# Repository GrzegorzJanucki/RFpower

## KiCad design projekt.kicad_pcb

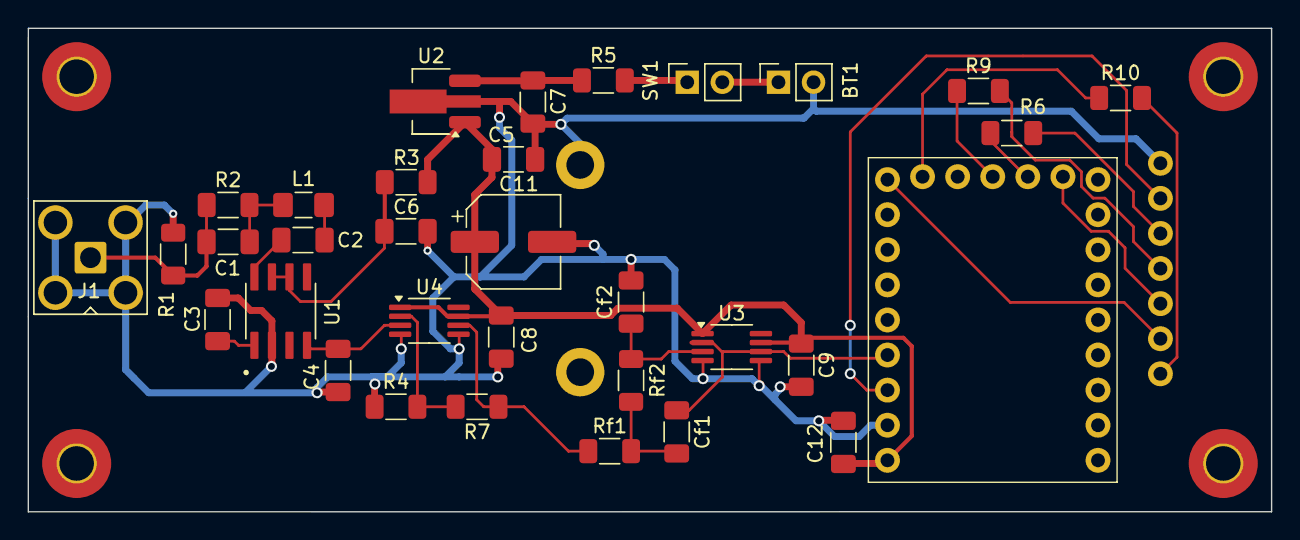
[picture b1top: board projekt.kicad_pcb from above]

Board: 2 copper layers, 90.0 x 35.0 mm, 34 parts (1 on the bottom side), 26 nets.

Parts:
BT1: 9V; PinSocket_1x02_P2.54mm_Vertical
C1: 15p; C_1206_3216Metric_Pad1.33x1.80mm_HandSolder
C2: 10n; C_1206_3216Metric_Pad1.33x1.80mm_HandSolder
C3, C4, C6, C8, C9, C12: 100n; C_1206_3216Metric_Pad1.33x1.80mm_HandSolder
C5, C7: 220n; C_1206_3216Metric_Pad1.33x1.80mm_HandSolder
C11: 10u; CP_Elec_6.3x5.3
Cf1, Cf2: 20n; C_1206_3216Metric_Pad1.33x1.80mm_HandSolder
J1: Conn_Coaxial; SMA_Amphenol_901-143_Horizontal
J2: OLED
L1: L; L_1206_3216Metric_Pad1.42x1.75mm_HandSolder
R1: 51; R_1206_3216Metric_Pad1.30x1.75mm_HandSolder
R2: 470; R_1206_3216Metric_Pad1.30x1.75mm_HandSolder
R3, R5: 6.8; R_1206_3216Metric_Pad1.30x1.75mm_HandSolder
R4: 3.3k; R_1206_3216Metric_Pad1.30x1.75mm_HandSolder
R6, R9, R10: 10; R_1206_3216Metric_Pad1.30x1.75mm_HandSolder
R7: 4.7k; R_1206_3216Metric_Pad1.30x1.75mm_HandSolder
RP2040-zero1: RP2040_0
Rf1, Rf2: 10k; R_1206_3216Metric_Pad1.30x1.75mm_HandSolder
SW1: SW_DIP_x01; PinSocket_1x02_P2.54mm_Vertical
U1: AD8307; SOIC127P600X175-8N
U2: L7805; SOT-89-3_Handsoldering
U3, U4: MSOP-8_3x3mm_P0.65mm

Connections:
/RF/A: C4.1, U1.4 (OUT), U4.3 (+)
/RF/RF+: C2.2, U1.8 (INP)
/RF/RF-: C3.2, U1.1 (INM)
/RF/RF_OUT: Cf1.1, RP2040-zero1.4 (GP29), U3.2 (-), U3.6
/uC/3V3: J2.2, RP2040-zero1.3 (3V3)
/uC/CS: J2.7, R10.2
/uC/DC: J2.6, RP2040-zero1.9 (GP14)
/uC/RST: J2.5, RP2040-zero1.14 (GP9)
/uC/SCK: J2.3, R6.2
/uC/SDA: J2.4, R9.2
GNDPWR: BT1.2 (-), C3.1, C4.2, C5.2, C6.2, C7.2, C8.2, C9.2, C11.2, C12.1, Cf2.2, J1.2 (Ext), J2.1, J2.8, R1.2, R4.1, RP2040-zero1.2 (GND), U1.2 (GND), U2.2 (GND), U3.4 (V-), U3.5 (SD), U4.4 (V-), U4.5 (SD)
unnamed: C1.2, L1.1, R2.2
unnamed: C2.1, L1.2
unnamed: Cf1.2, Rf1.2, Rf2.1
unnamed: C1.1, J1.1 (In), R1.1, R2.1
unnamed: R5.2, SW1.1
unnamed: R7.1, Rf1.1, U4.6
unnamed: R6.1, RP2040-zero1.13 (GP10)
unnamed: R9.1, RP2040-zero1.12 (GP11)
unnamed: R10.1, RP2040-zero1.10 (GP13)
unnamed: C6.1, R3.1, U1.6 (ENB), U1.7 (VCC)
unnamed: C7.1, R5.1, U2.3 (IN)
unnamed: Cf2.1, Rf2.2, U3.3 (+)
unnamed: R4.2, R7.2, U4.2 (-)
VCC: C5.1, C8.1, C9.1, C11.1, C12.2, R3.2, RP2040-zero1.1 (5V), U2.1 (OUT), U3.1 (SL), U3.7 (V+), U4.1 (SL), U4.7 (V+)
V_BAT: BT1.1 (+), SW1.2

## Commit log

2024-08-01 wersja 1.0 - próba GIT-a
2024-08-08 dodany kondensator na wyjściu VRM
2024-08-08 dodane C10
2024-08-08 C11 przeniesiony
2024-08-08 test111
2024-08-08 test2
2024-08-08 Kondensator usunięty Test2
2024-08-08 poprawione ścieżki
2024-08-09 ostatnie zmiany 09.08.2024
2024-08-20 usunięte część ostrzeżeń i błędów
2024-08-23 ostateczna wersja do produkcji
2024-09-04 wersja wysłana do produkcji
2024-09-26 poprawione piny RP2040 na płytce
